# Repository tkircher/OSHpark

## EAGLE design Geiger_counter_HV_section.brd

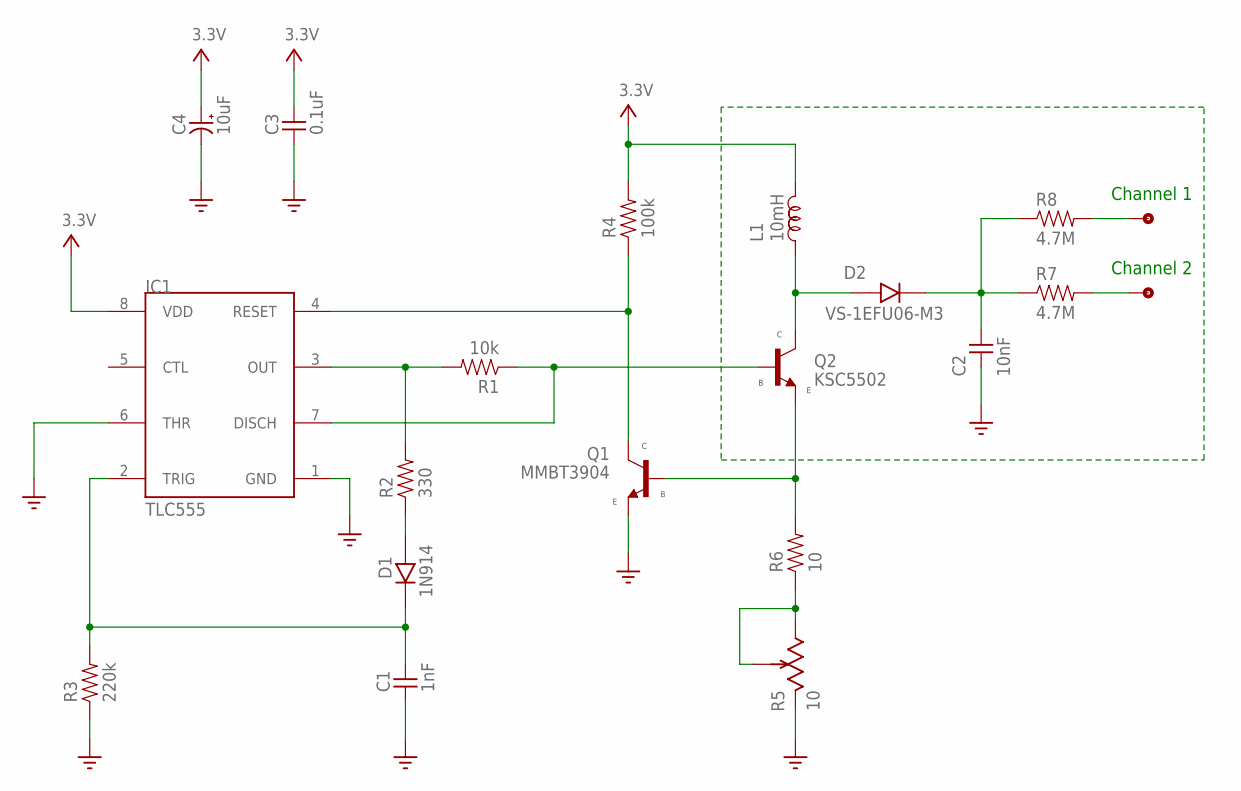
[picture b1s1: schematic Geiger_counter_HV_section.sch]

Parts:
C1: 1nF; 0805
C2: 10nF; 1206
C3: 0.1uF; 0805
C4: 10uF; 1206
D1: 1N914; 0805
D2: VS-1EFU06-M3; DO-219AB
IC1: TLC555; SOIC8
L1: 10mH; 1200LRS
Q1: MMBT3904; SOT-23A
Q2: KSC5502; TO-252
R1: 10k; 0805
R2: 330; 0805
R3: 220k; 0805
R4: 100k; 0805
R5: 10; 3362P
R6: 10; 1206
R7, R8: 4.7M; 1206
TP1, TP2: TP

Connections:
GND: C1.1, C2.1, C3.1, C4.2, IC1.1 (GND), IC1.6 (THR), Q1.3 (E), R3.1, R5.P$3 (P3)
unnamed: D1.1 (A), R2.1
unnamed: IC1.4 (RESET), Q1.1 (C), R4.1
unnamed: IC1.3 (OUT), R1.2, R2.2
unnamed: R5.P$1 (P1), R5.P$2 (WIPE), R6.1
unnamed: Q1.2 (B), Q2.P$2 (E), R6.2
unnamed: C1.2, D1.2 (K), IC1.2 (TRIG), R3.2
unnamed: IC1.7 (DISCH), Q2.P$1 (B), R1.1
unnamed: C2.2, D2.P$2 (K), R7.1, R8.1
unnamed: R7.2, TP1.P$1
unnamed: D2.P$1 (A), L1.P1 (1), Q2.P$3 (C)
unnamed: R8.2, TP2.P$1
VCC: C3.2, C4.1, IC1.8 (VDD), L1.P3 (2), R4.2

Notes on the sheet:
Channel 1
Channel 2

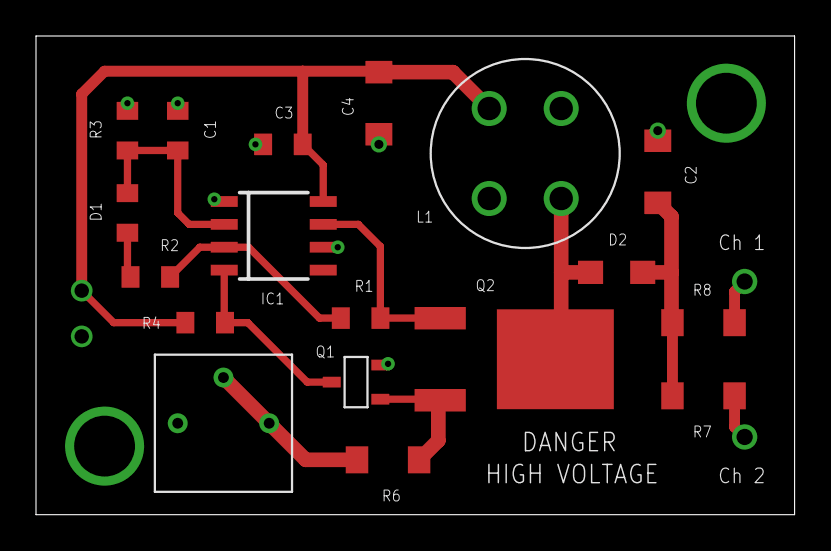
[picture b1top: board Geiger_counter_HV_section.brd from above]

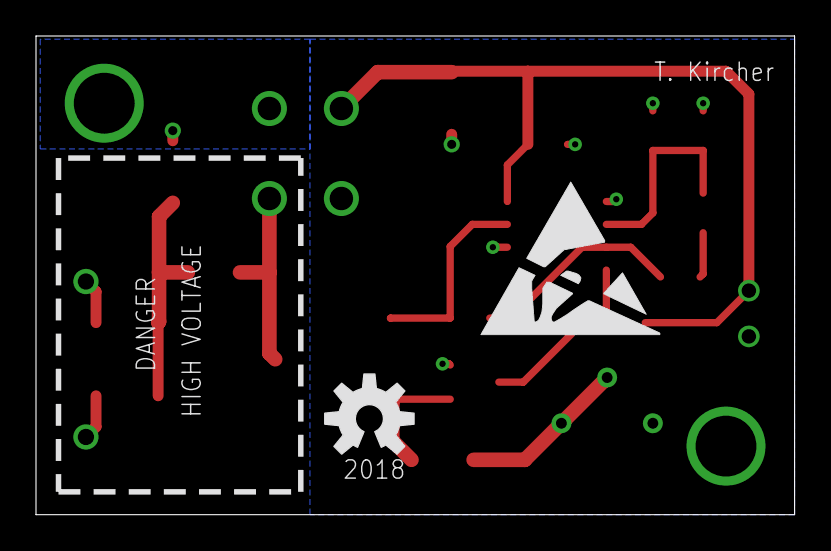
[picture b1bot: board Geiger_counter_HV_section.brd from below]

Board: 2 copper layers, 42.1 x 26.6 mm, 22 parts (2 on the bottom side), 13 nets.

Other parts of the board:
U$14: ESD_10.00
U$15: OSHW-LOGO-M

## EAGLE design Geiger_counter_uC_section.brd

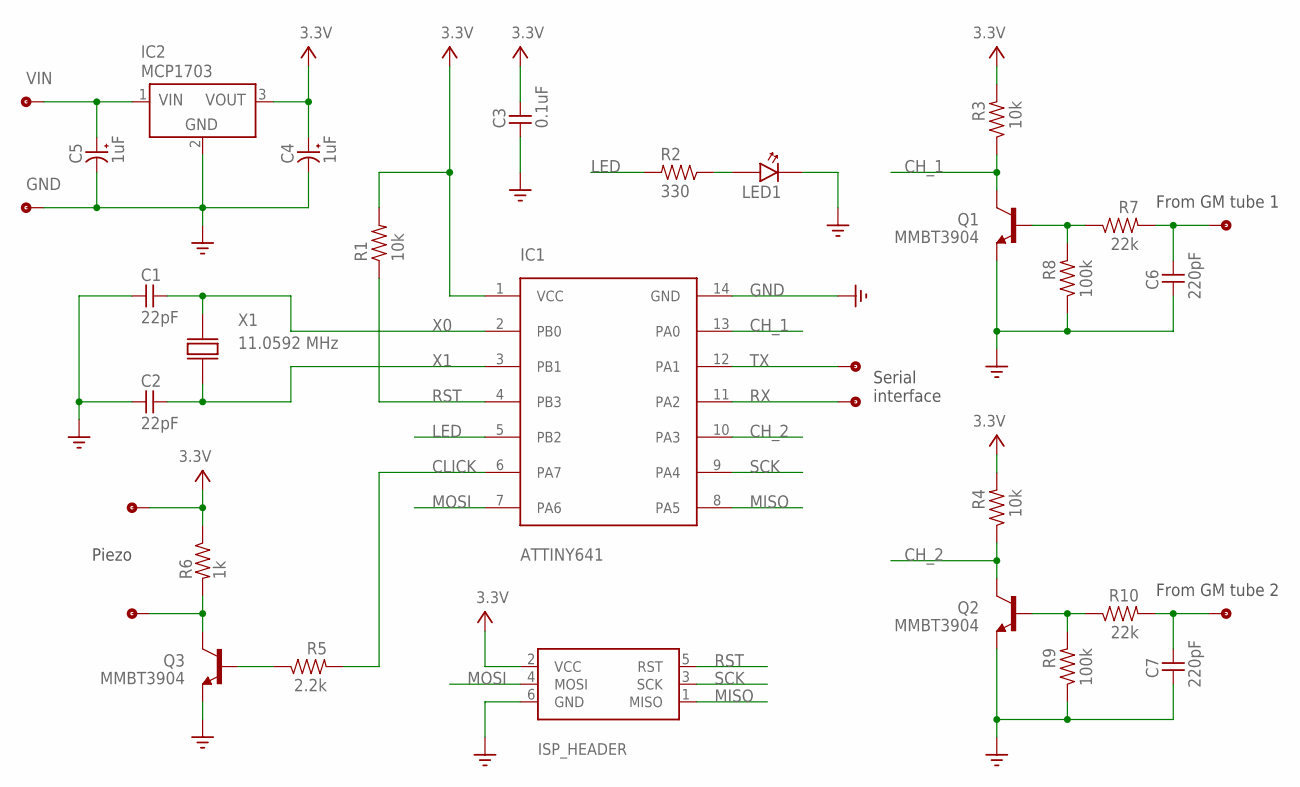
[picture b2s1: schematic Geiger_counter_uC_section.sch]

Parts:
C1, C2: 22pF; 0805
C3: 0.1uF; 0805
C4, C5: 1uF; 1206
C6, C7: 220pF; 0805
IC1: ATTINY641; SO14
IC2: MCP1703; SOT-23A
ISP_HEADER: ISP header; ISP_HEADER
LED1: LED0805; 0805
Q1, Q2, Q3: MMBT3904; SOT-23A
R1, R3, R4: 10k; 0805
R2: 330; 0805
R5: 2.2k; 0805
R6: 1k; 0805
R7, R10: 22k; 0805
R8, R9: 100k; 0805
TP1, TP2, TP3, TP4, TP7, TP8: TPSMALL; TP_SMALL
TP5, TP6: TP
X1: 11.0592 MHz; ABM3-2SMD

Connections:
3V3: C3.2, C4.1, IC1.1 (VCC), IC2.3 (VOUT), ISP_HEADER.2 (VCC), R1.2, R3.2, R4.2, R6.1, TP4.TP_SMALL
CH_1: IC1.13 (PA0), Q1.1 (C), R3.1
CH_2: IC1.10 (PA3), Q2.1 (C), R4.1
CLICK: IC1.6 (PA7), R5.2
GND: C1.1, C2.1, C3.1, C4.2, C5.2, C6.2, C7.2, IC1.14 (GND), IC2.2 (GND), ISP_HEADER.6 (GND), LED1.2 (K), Q1.3 (E), Q2.3 (E), Q3.3 (E), R8.1, R9.1, TP8.TP_SMALL
LED: IC1.5 (PB2), R2.2
MISO: IC1.8 (PA5), ISP_HEADER.1 (MISO)
MOSI: IC1.7 (PA6), ISP_HEADER.4 (MOSI)
unnamed: LED1.1 (A), R2.1
unnamed: Q3.2 (B), R5.1
unnamed: Q3.1 (C), R6.2, TP3.TP_SMALL
unnamed: Q1.2 (B), R7.1, R8.2
unnamed: C6.1, R7.2, TP5.P$1
unnamed: Q2.2 (B), R9.2, R10.1
unnamed: C7.1, R10.2, TP6.P$1
RST: IC1.4 (PB3), ISP_HEADER.5 (RST), R1.1
RX: IC1.11 (PA2), TP2.TP_SMALL
SCK: IC1.9 (PA4), ISP_HEADER.3 (SCK)
TX: IC1.12 (PA1), TP1.TP_SMALL
VIN: C5.1, IC2.1 (VIN), TP7.TP_SMALL
X0: C1.2, IC1.2 (PB0), X1.P$2 (2)
X1: C2.2, IC1.3 (PB1), X1.P$1 (1)

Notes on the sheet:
Serial interface
Piezo
From GM tube 1
From GM tube 2

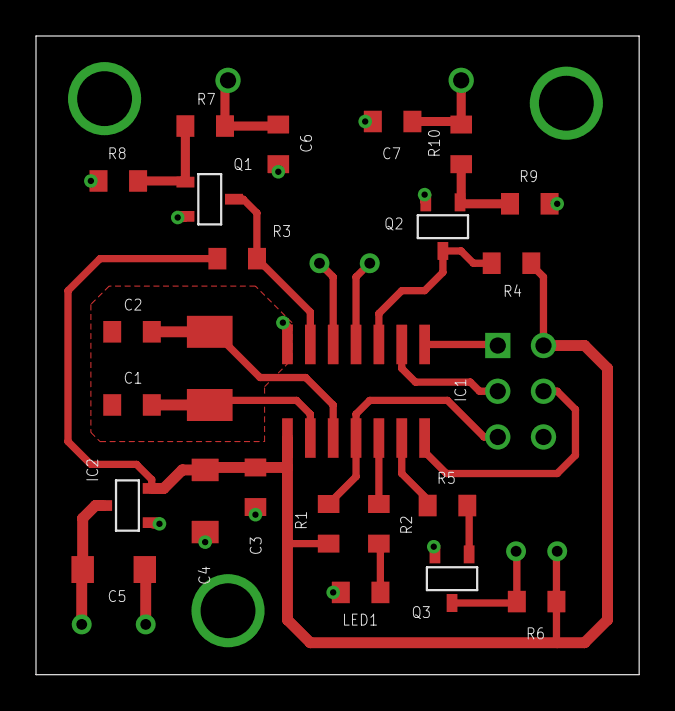
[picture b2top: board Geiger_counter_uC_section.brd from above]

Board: 2 copper layers, 33.5 x 35.5 mm, 34 parts (1 on the bottom side), 22 nets.

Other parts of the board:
U$17: OSHW-LOGO-M

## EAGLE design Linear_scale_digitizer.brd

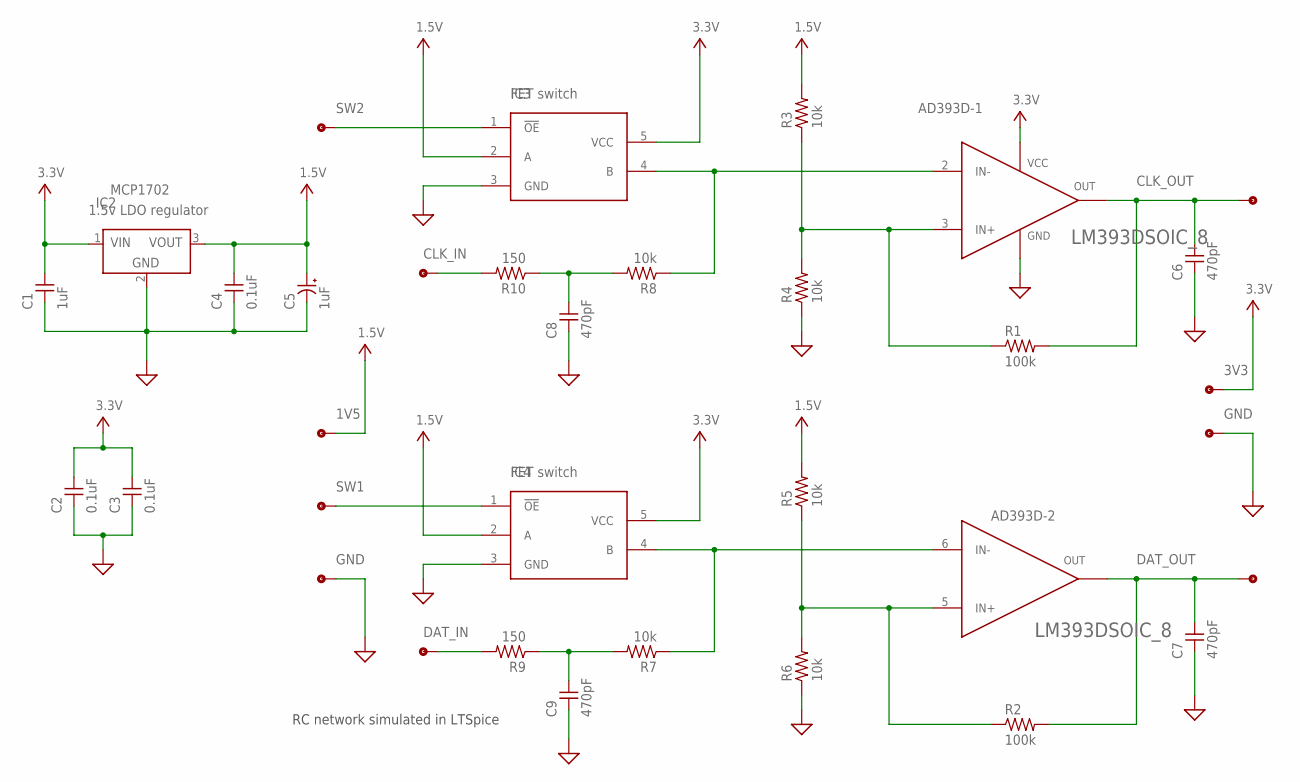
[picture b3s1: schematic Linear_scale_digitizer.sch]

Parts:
C1, C5: 1uF; 0805
C2, C3, C4: 0.1uF; 0805
C6, C7, C8, C9: 470pF; 0805
IC1: LM393DSOIC_8; SO_8
IC2: MCP1702; SOT-23A
IC3, IC4: SN74CB3T1G125; SOT_23-5
R1, R2: 100k; 0805
R3, R4, R5, R6, R7, R8: 10k; 0805
R9, R10: 150; 0805
TP1, TP2, TP3, TP4, TP5, TP6, TP7, TP8, TP9, TP10: TP

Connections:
1V5: C4.2, C5.1, IC2.3 (VOUT), IC3.2 (A), IC4.2 (A), R3.2, R5.2, TP7.P$1
3V3: C1.2, C2.2, C3.2, IC1.8 (VCC), IC2.1 (VIN), IC3.5 (VCC), IC4.5 (VCC), TP10.P$1
CLK_IN: R10.2, TP5.P$1
CLK_OUT: C6.2, IC1.1 (OUT), R1.2, TP1.P$1
DAT_IN: R9.2, TP6.P$1
DAT_OUT: C7.2, IC1.7 (OUT), R2.2, TP2.P$1
GND: C1.1, C2.1, C3.1, C4.1, C5.2, C6.1, C7.1, C8.1, C9.1, IC1.4 (GND), IC2.2 (GND), IC3.3 (GND), IC4.3 (GND), R4.1, R6.1, TP8.P$1, TP9.P$1
unnamed: IC1.5 (IN+), R2.1, R5.1, R6.2
unnamed: IC1.3 (IN+), R1.1, R3.1, R4.2
unnamed: C8.2, R8.2, R10.1
unnamed: IC1.6 (IN-), IC4.4 (B), R7.1
unnamed: IC1.2 (IN-), IC3.4 (B), R8.1
unnamed: C9.2, R7.2, R9.1
SW1: IC4.1 (!OE), TP4.P$1
SW2: IC3.1 (!OE), TP3.P$1

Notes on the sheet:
1.5v LDO regulator
FET switch
AD393D-2
AD393D-1
RC network simulated in LTSpice

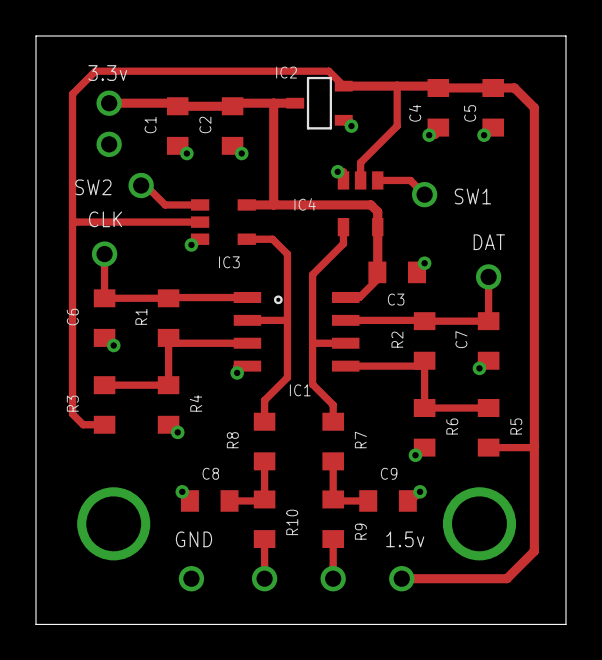
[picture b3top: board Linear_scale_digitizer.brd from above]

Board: 2 copper layers, 29.4 x 32.7 mm, 34 parts (1 on the bottom side), 15 nets.

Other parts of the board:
U$7: ESD_10.00

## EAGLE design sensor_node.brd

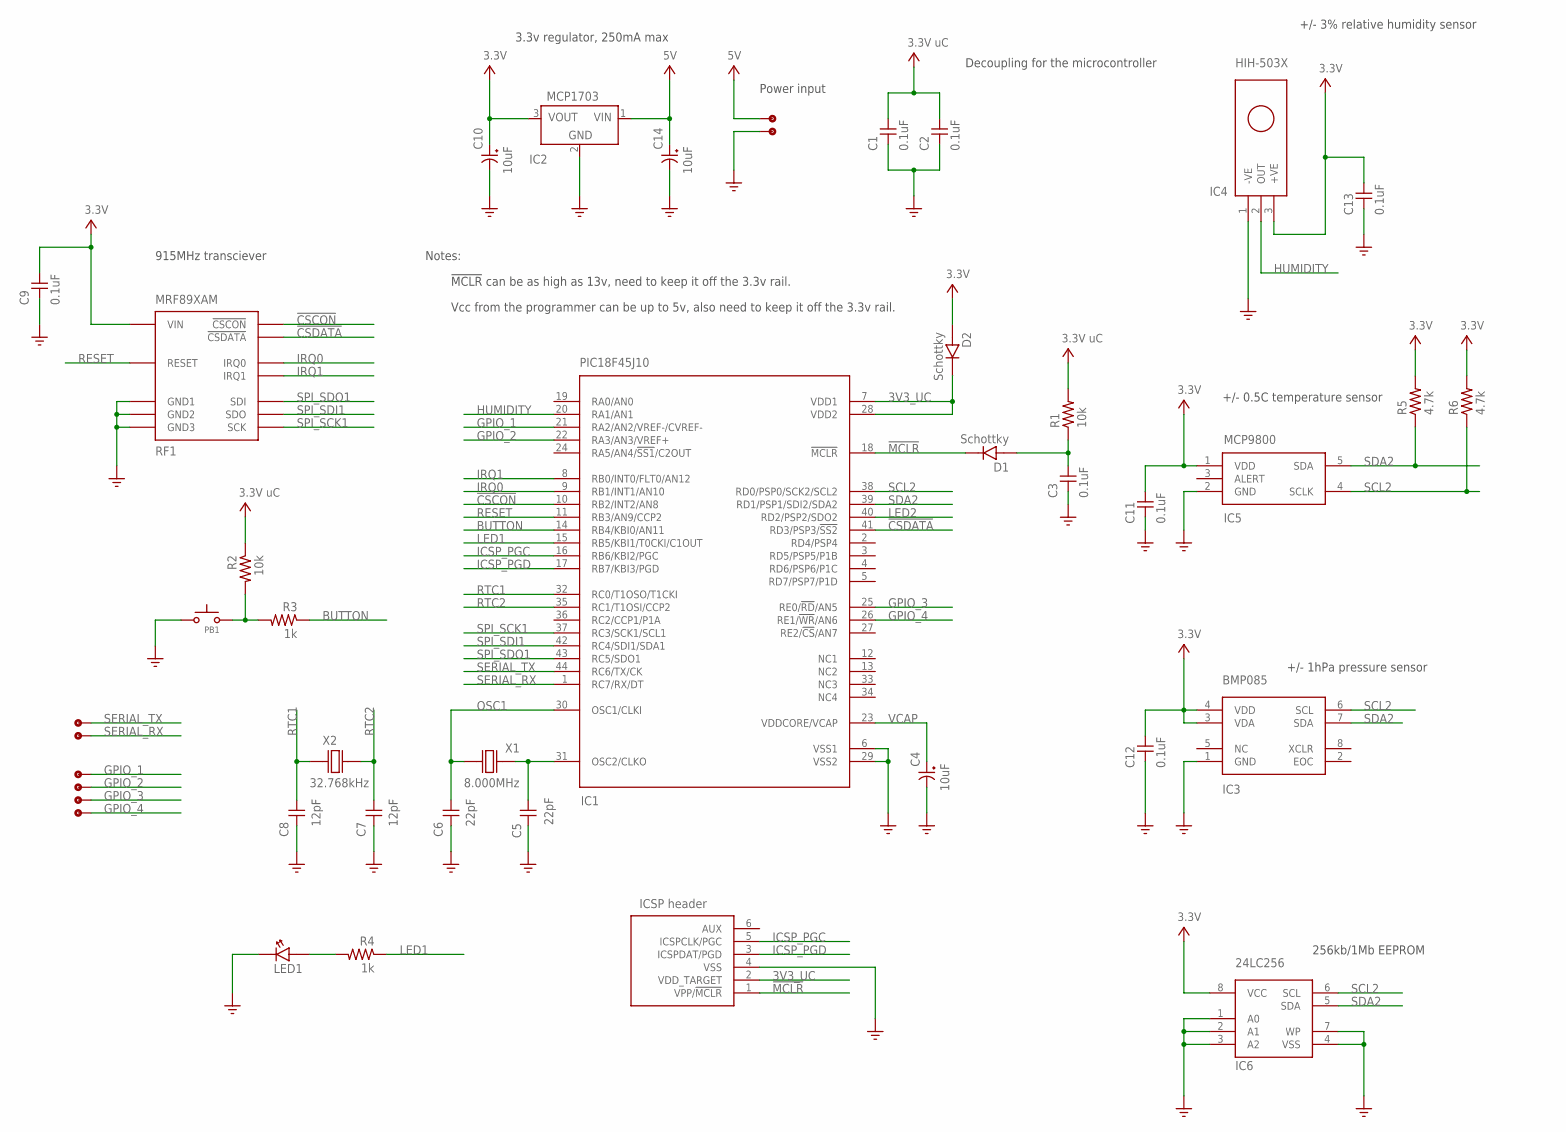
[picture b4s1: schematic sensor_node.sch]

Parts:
C1, C2, C3, C9, C11, C12, C13: 0.1uF; 0805
C4, C10, C14: 10uF; 1206
C5, C6: 22pF; 0805
C7, C8: 12pF; 0805
CONN1: ICSP header; ISP_HEADER
D1, D2: Schottky; 0805
IC1: PIC18F45J10; TQFP_44
IC2: MCP1703; SOT-23A
IC3: BMP085; LCC8
IC4: HIH-503X; HIH_503X
IC5: MCP9800; SOT_23-5
IC6: 24LC256; SO_8
LED1: LED0805; 0805
PB1: BUTTON_2PADS; BUTTON_4SMD
R1, R2: 10k; 0805
R3, R4: 1k; 0805
R5, R6: 4.7k; 0805
RF1: MRF89XAM
TP1, TP2, TP3, TP4, TP5, TP6, TP7, TP8: TP
X1: 8.000MHz; NX5032
X2: 32.768kHz; CM200C

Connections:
3V3: C9.2, C10.1, C11.2, C12.2, C13.2, D2.1 (A), IC2.3 (VOUT), IC3.3 (VDA), IC3.4 (VDD), IC4.3 (+VE), IC5.1 (VDD), IC6.8 (VCC), R5.2, R6.2, RF1.VIN
3V3_UC: C1.2, C2.2, CONN1.2 (VDD_TARGET), D2.2 (K), IC1.7 (VDD1), IC1.28 (VDD2), R1.2, R2.1
5V: C14.1, IC2.1 (VIN), TP3.P$1
!CSCON!: IC1.10 (RB2/INT2/AN8), RF1.!CSCON
!CSDATA!: IC1.41 (RD3/PSP3/!SS2!), RF1.!CSDATA
!MCLR!: CONN1.1 (VPP/!MCLR!), D1.2 (K), IC1.18 (!MCLR!)
BUTTON: IC1.14 (RB4/KBI0/AN11), R3.1
GND: C1.1, C2.1, C3.1, C4.2, C5.2, C6.2, C7.2, C8.2, C9.1, C10.2, C11.1, C12.1, C13.1, C14.2, CONN1.4 (VSS), IC1.6 (VSS1), IC1.29 (VSS2), IC2.2 (GND), IC3.1 (GND), IC4.1 (-VE), IC5.2 (GND), IC6.1 (A0), IC6.2 (A1), IC6.3 (A2), IC6.4 (VSS), IC6.7 (WP), LED1.2 (K), PB1.3, RF1.GND1, RF1.GND2, RF1.GND3, TP4.P$1
GPIO_1: IC1.21 (RA2/AN2/VREF-/CVREF-), TP6.P$1
GPIO_2: IC1.22 (RA3/AN3/VREF+), TP5.P$1
GPIO_3: IC1.25 (RE0/!RD!/AN5), TP7.P$1
GPIO_4: IC1.26 (RE1/!WR!/AN6), TP8.P$1
HUMIDITY: IC1.20 (RA1/AN1), IC4.2 (OUT)
ICSP_PGC: CONN1.5 (ICSPCLK/PGC), IC1.16 (RB6/KBI2/PGC)
ICSP_PGD: CONN1.3 (ICSPDAT/PGD), IC1.17 (RB7/KBI3/PGD)
IRQ0: IC1.9 (RB1/INT1/AN10), RF1.IRQ0
IRQ1: IC1.8 (RB0/INT0/FLT0/AN12), RF1.IRQ1
LED1: IC1.15 (RB5/KBI1/T0CKI/C1OUT), R4.1
LED2: IC1.40 (RD2/PSP2/SDO2)
unnamed: LED1.1 (A), R4.2
unnamed: C3.2, D1.1 (A), R1.1
unnamed: PB1.1, R2.2, R3.2
OSC1: C6.1, IC1.30 (OSC1/CLKI), X1.P$1 (1)
OSC2: C5.1, IC1.31 (OSC2/CLKO), X1.P$2 (2)
RESET: IC1.11 (RB3/AN9/CCP2), RF1.RESET
RTC1: C8.1, IC1.32 (RC0/T1OSO/T1CKI), X2.OSC2 (2)
RTC2: C7.1, IC1.35 (RC1/T1OSI/CCP2), X2.OSC1 (1)
SCL2: IC1.38 (RD0/PSP0/SCK2/SCL2), IC3.6 (SCL), IC5.4 (SCLK), IC6.6 (SCL), R6.1
SDA2: IC1.39 (RD1/PSP1/SDI2/SDA2), IC3.7 (SDA), IC5.5 (SDA), IC6.5 (SDA), R5.1
SERIAL_RX: IC1.1 (RC7/RX/DT), TP2.P$1
SERIAL_TX: IC1.44 (RC6/TX/CK), TP1.P$1
SPI_SCK1: IC1.37 (RC3/SCK1/SCL1), RF1.SCK
SPI_SDI1: IC1.42 (RC4/SDI1/SDA1), RF1.SDO
SPI_SDO1: IC1.43 (RC5/SDO1), RF1.SDI
VCAP: C4.1, IC1.23 (VDDCORE/VCAP)

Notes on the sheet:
915MHz transciever
+/- 0.5C temperature sensor
+/- 1hPa pressure sensor
+/- 3% relative humidity sensor
3.3v regulator, 250mA max
Power input
256kb/1Mb EEPROM
!MCLR! can be as high as 13v, need to keep it off the 3.3v rail.
Vcc from the programmer can be up to 5v, also need to keep it off the 3.3v rail.
Notes:
Decoupling for the microcontroller

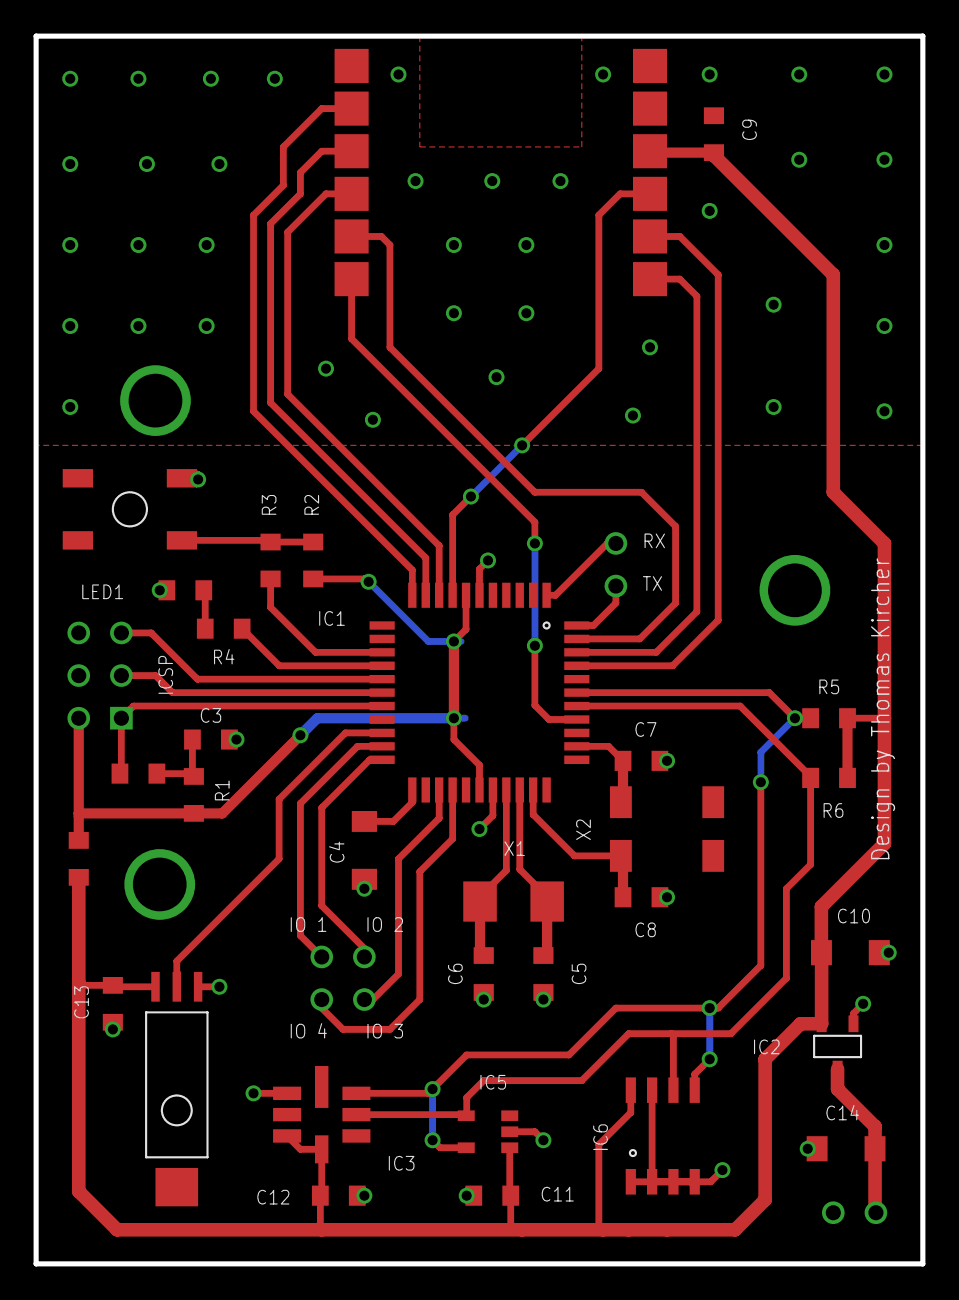
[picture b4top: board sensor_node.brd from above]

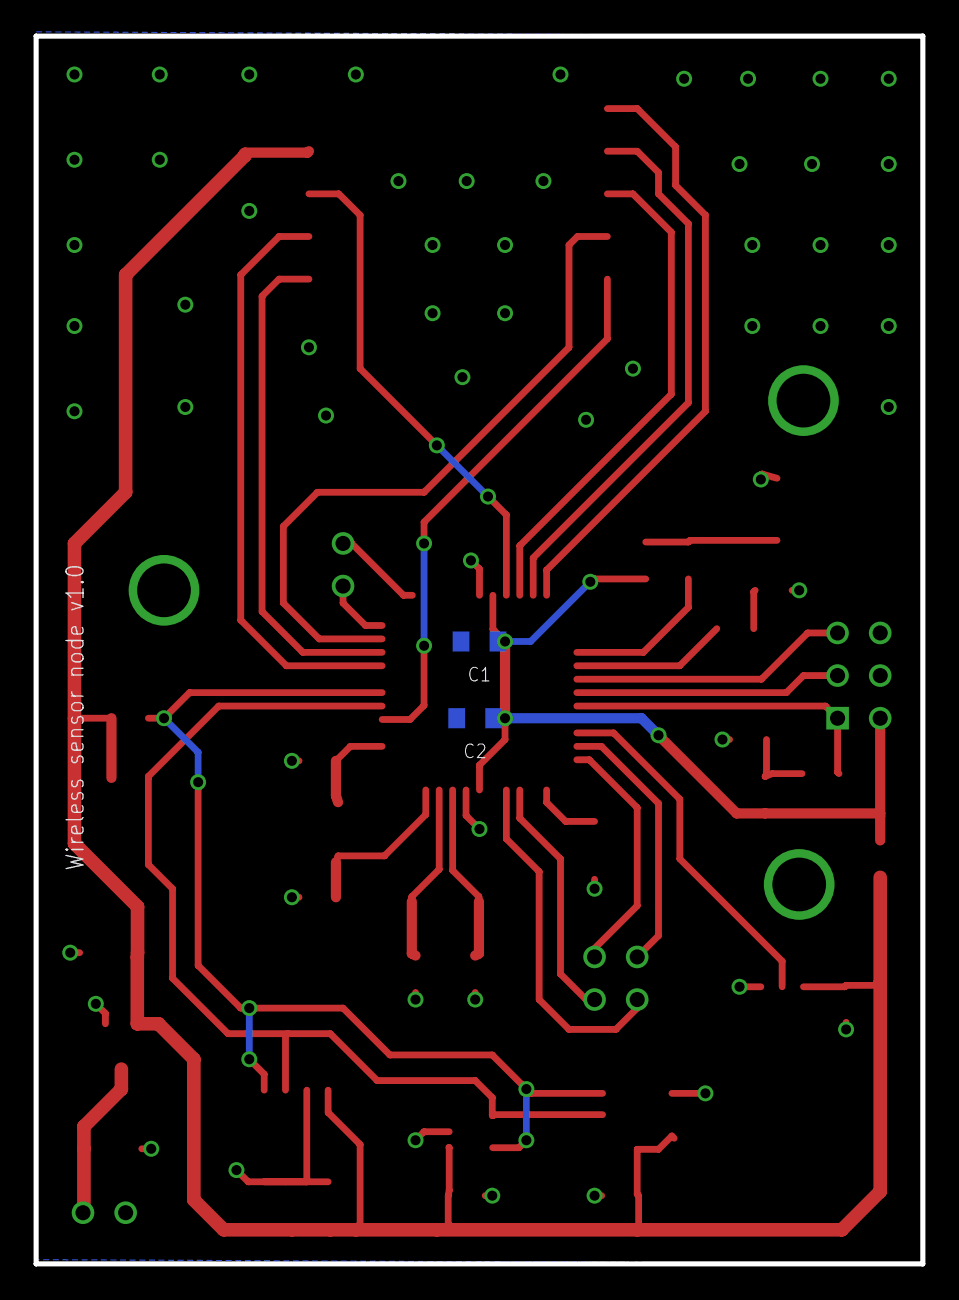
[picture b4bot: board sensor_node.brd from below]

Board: 2 copper layers, 52.8 x 73.2 mm, 43 parts (3 on the bottom side), 34 nets.

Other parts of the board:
OSHLOGO: OSHLOGO

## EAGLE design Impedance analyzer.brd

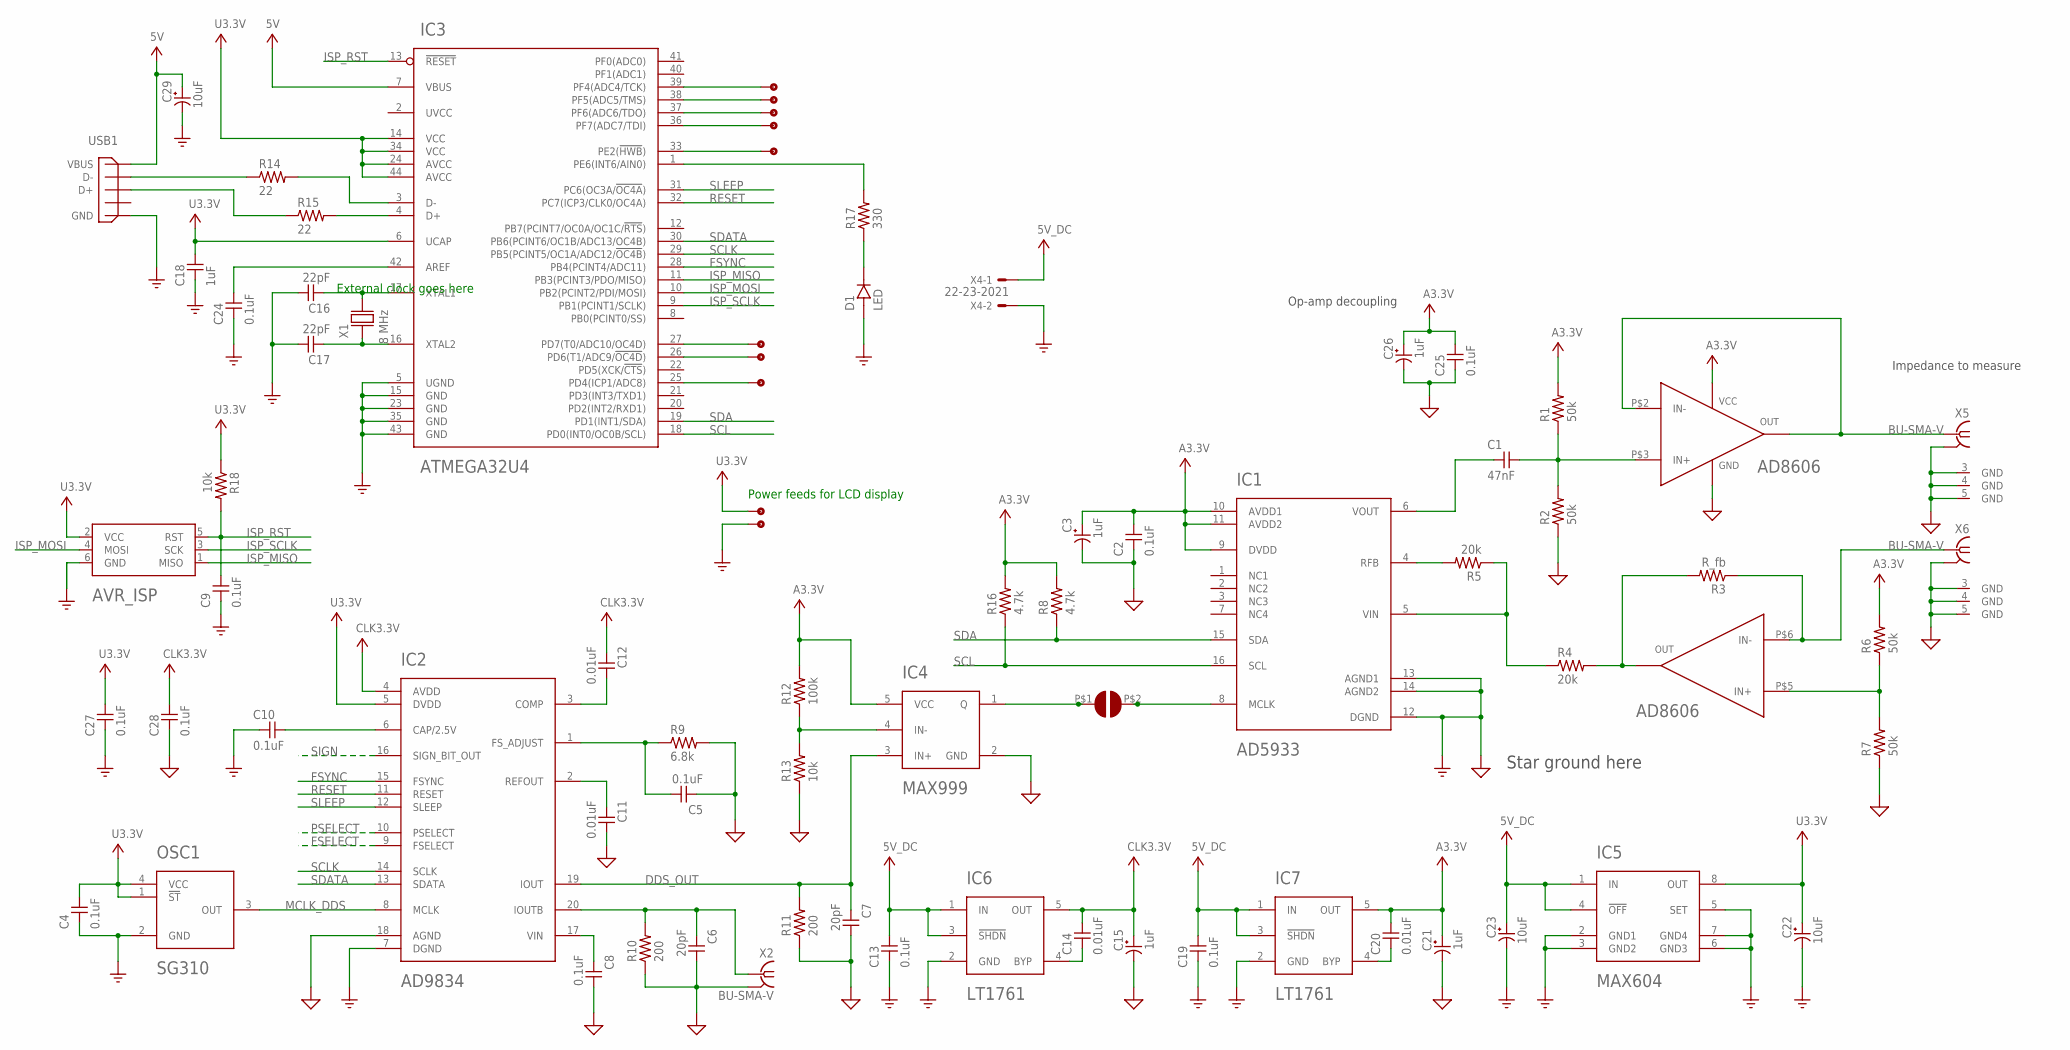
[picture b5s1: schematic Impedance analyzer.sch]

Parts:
C1: 47nF; 0805
C2, C4, C5, C8, C9, C10, C13, C19, C24, C25, C27, C28: 0.1uF; 0805
C3, C15, C21, C26: 1uF; 1206
C6, C7: 20pF; 0805
C11, C12, C14, C20: 0.01uF; 0805
C16, C17: 22pF; 0805
C18: 1uF; 0805
C22, C23, C29: 10uF; 1206
D1: LED; 0805
IC1: AD5933; SSOP_16
IC2: AD9834; TSSOP_20
IC3: ATMEGA32U4; TQFP_44
IC4: MAX999; SOT_23-5
IC5: MAX604; SO_8
IC6, IC7: LT1761; TSOT-23
IC8: AD8606; MSOP_8
OSC1: SG310
R1, R2, R6, R7: 50k; 0805
R3: R_fb; 0805
R4, R5: 20k; 0805
R8, R16: 4.7k; 0805
R9: 6.8k; 0805
R10, R11: 200; 0805
R12: 100k; 0805
R13, R18: 10k; 0805
R14, R15: 22; 0805
R17: 330; 0805
TP1, TP2, TP3, TP4, TP5, TP6, TP7, TP10, TP11, TP12: TPSMALL; TP_SMALL
U$41: ISP_HEADER
U$57: JUMPER
USB1: USB_MINIUX60-MB-5ST; USB_MINI
X1: 8 MHz; NX5032
X2, X5, X6: BU-SMA-V
X4: 22-23-2021

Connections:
5V_DC: C13.2, C19.2, C23.1, IC5.1 (IN), IC5.4 (!OFF), IC6.1 (IN), IC6.3 (!SHDN), IC7.1 (IN), IC7.3 (!SHDN), X4.1
5V_USB: C29.1, IC3.7 (VBUS), USB1.1 (VBUS)
A3V3: C2.2, C3.1, C20.2, C21.1, C25.2, C26.1, IC1.9 (DVDD), IC1.10 (AVDD1), IC1.11 (AVDD2), IC4.5 (VCC), IC7.5 (OUT), IC8.P$8 (VCC), R1.2, R6.2, R8.2, R12.2, R16.2
CLK3V3: C12.1, C14.2, C15.1, C28.2, IC2.4 (AVDD), IC6.5 (OUT)
DDS_OUT: C7.1, IC2.19 (IOUT), IC4.3 (IN+), R11.2
FSELECT: IC2.9 (FSELECT)
FSYNC: IC2.15 (FSYNC), IC3.28 (PB4(PCINT4/ADC11))
GND: C2.1, C3.2, C4.1, C5.1, C6.2, C7.2, C8.2, C9.1, C10.1, C11.2, C13.1, C15.2, C16.2, C17.2, C18.1, C19.1, C21.2, C22.2, C23.2, C24.1, C25.1, C26.2, C27.1, C28.1, C29.2, D1.1 (A), IC1.12 (DGND), IC1.13 (AGND1), IC1.14 (AGND2), IC2.7 (DGND), IC2.18 (AGND), IC3.5 (UGND), IC3.15 (GND), IC3.23 (GND), IC3.35 (GND), IC3.43 (GND), IC4.2 (GND), IC5.2 (GND1), IC5.3 (GND2), IC5.5 (SET), IC5.6 (GND3), IC5.7 (GND4), IC6.2 (GND), IC7.2 (GND), IC8.P$4 (GND), OSC1.2 (GND), R2.1, R7.1, R9.2, R10.1, R11.1, R13.1, TP11.TP_SMALL, U$41.6 (GND), USB1.5 (GND), X2.2 (GND), X2.3 (GND), X2.4 (GND), X2.5 (GND), X4.2, X5.2 (GND), X5.3 (GND), X5.4 (GND), X5.5 (GND), X6.2 (GND), X6.3 (GND), X6.4 (GND), X6.5 (GND)
ISP_MISO: IC3.11 (PB3(PCINT3/PDO/MISO)), U$41.1 (MISO)
ISP_MOSI: IC3.10 (PB2(PCINT2/PDI/MOSI)), U$41.4 (MOSI)
ISP_RST: C9.2, IC3.13 (!RESET!), R18.2, U$41.5 (RST)
ISP_SCLK: IC3.9 (PB1(PCINT1/SCLK)), U$41.3 (SCK)
MCLK_DDS: IC2.8 (MCLK), OSC1.3 (OUT)
unnamed: C1.2, IC8.P$3 (IN+), R1.1, R2.2
unnamed: IC8.P$1 (OUT), IC8.P$2 (IN-), X5.1
unnamed: IC8.P$6 (IN-), R3.1, X6.1
unnamed: IC8.P$7 (OUT), R3.2, R4.2
unnamed: IC8.P$5 (IN+), R6.1, R7.2
unnamed: IC1.4 (RFB), R5.2
unnamed: IC1.5 (VIN), R4.1, R5.1
unnamed: C1.1, IC1.6 (VOUT)
unnamed: IC3.1 (PE6(INT6/AIN0)), R17.2
unnamed: C24.2, IC3.42 (AREF)
unnamed: C5.2, IC2.1 (FS_ADJUST), R9.1
unnamed: C6.1, IC2.20 (IOUTB), R10.2, X2.1
unnamed: C10.2, IC2.6 (CAP/2.5V)
unnamed: C11.1, IC2.2 (REFOUT)
unnamed: D1.2 (K), R17.1
unnamed: C8.1, IC2.17 (VIN)
unnamed: C12.2, IC2.3 (COMP)
unnamed: IC3.27 (PD7(T0/ADC10/OC4D)), TP1.TP_SMALL
unnamed: C14.1, IC6.4 (BYP)
unnamed: IC3.26 (PD6(T1/ADC9/!OC4D!)), TP2.TP_SMALL
unnamed: IC3.39 (PF4(ADC4/TCK)), TP3.TP_SMALL
unnamed: IC4.4 (IN-), R12.1, R13.2
unnamed: IC3.4 (D+), R15.2
unnamed: R15.1, USB1.3 (D+)
unnamed: R14.1, USB1.2 (D-)
unnamed: IC3.3 (D-), R14.2
unnamed: C16.1, IC3.17 (XTAL1), X1.P$2 (2)
unnamed: C17.1, IC3.16 (XTAL2), X1.P$1 (1)
unnamed: IC3.38 (PF5(ADC5/TMS)), TP4.TP_SMALL
unnamed: C20.1, IC7.4 (BYP)
unnamed: IC3.37 (PF6(ADC6/TDO)), TP5.TP_SMALL
unnamed: IC3.36 (PF7(ADC7/TDI)), TP6.TP_SMALL
unnamed: IC3.25 (PD4(ICP1/ADC8)), TP7.TP_SMALL
unnamed: IC4.1 (Q), U$57.P$1
unnamed: IC1.8 (MCLK), U$57.P$2
unnamed: IC3.33 (PE2(!HWB!)), TP12.TP_SMALL
PSELECT: IC2.10 (PSELECT)
RESET: IC2.11 (RESET), IC3.32 (PC7(ICP3/CLK0/OC4A))
SCL: IC1.16 (SCL), IC3.18 (PD0(INT0/OC0B/SCL)), R16.1
SCLK: IC2.14 (SCLK), IC3.29 (PB5(PCINT5/OC1A/ADC12/!OC4B!))
SDA: IC1.15 (SDA), IC3.19 (PD1(INT1/SDA)), R8.1
SDATA: IC2.13 (SDATA), IC3.30 (PB6(PCINT6/OC1B/ADC13/OC4B))
SIGN: IC2.16 (SIGN_BIT_OUT)
SLEEP: IC2.12 (SLEEP), IC3.31 (PC6(OC3A/!OC4A!))
U3V3: C4.2, C18.2, C22.1, C27.2, IC2.5 (DVDD), IC3.6 (UCAP), IC3.14 (VCC), IC3.24 (AVCC), IC3.34 (VCC), IC3.44 (AVCC), IC5.8 (OUT), OSC1.1 (!ST), OSC1.4 (VCC), R18.1, TP10.TP_SMALL, U$41.2 (VCC)

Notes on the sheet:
Impedance to measure
Op-amp decoupling
Star ground here
External clock goes here
Power feeds for LCD display

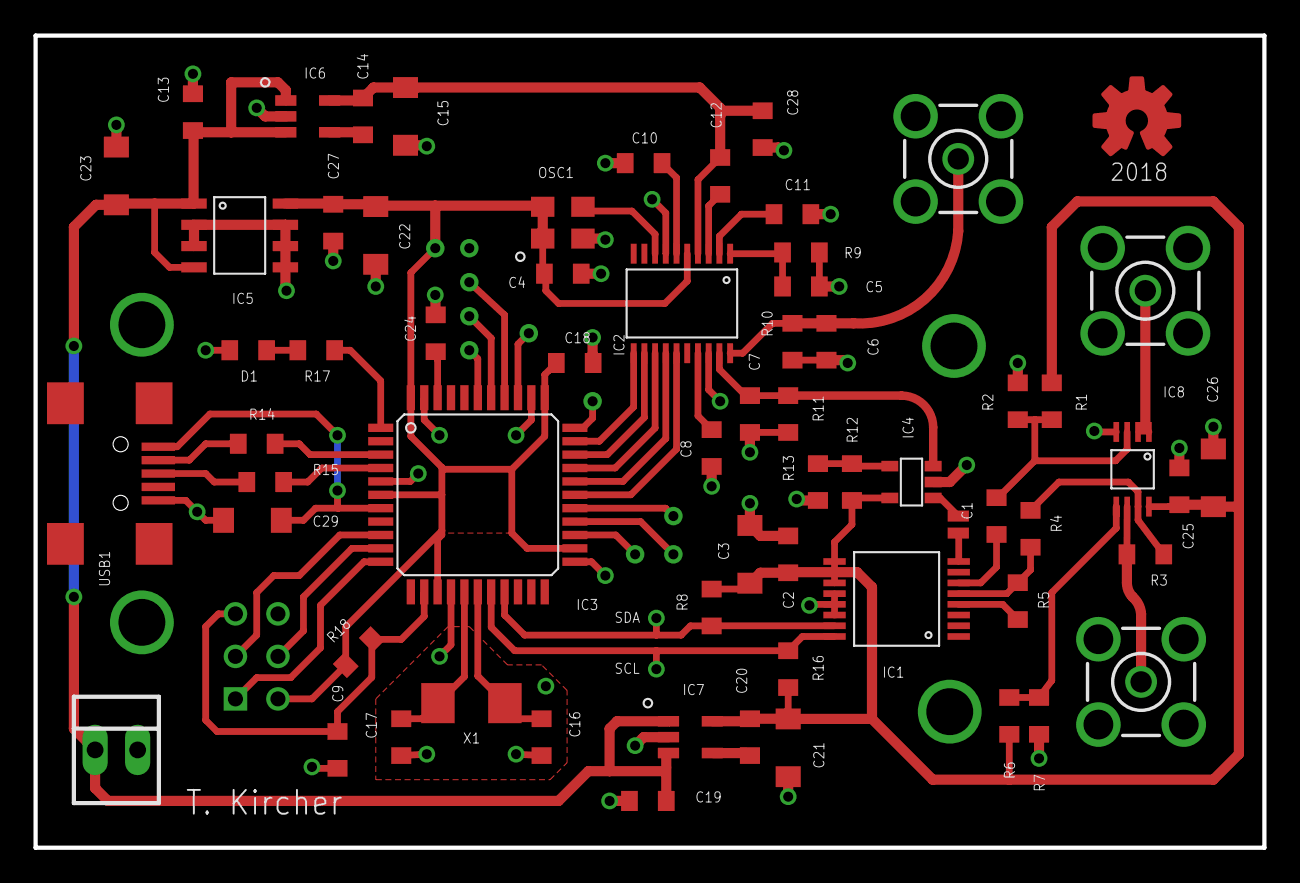
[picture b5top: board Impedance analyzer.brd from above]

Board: 2 copper layers, 73.4 x 48.5 mm, 76 parts (1 on the bottom side), 55 nets.

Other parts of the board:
U$1: OSHWLOGO_TOP_0.2

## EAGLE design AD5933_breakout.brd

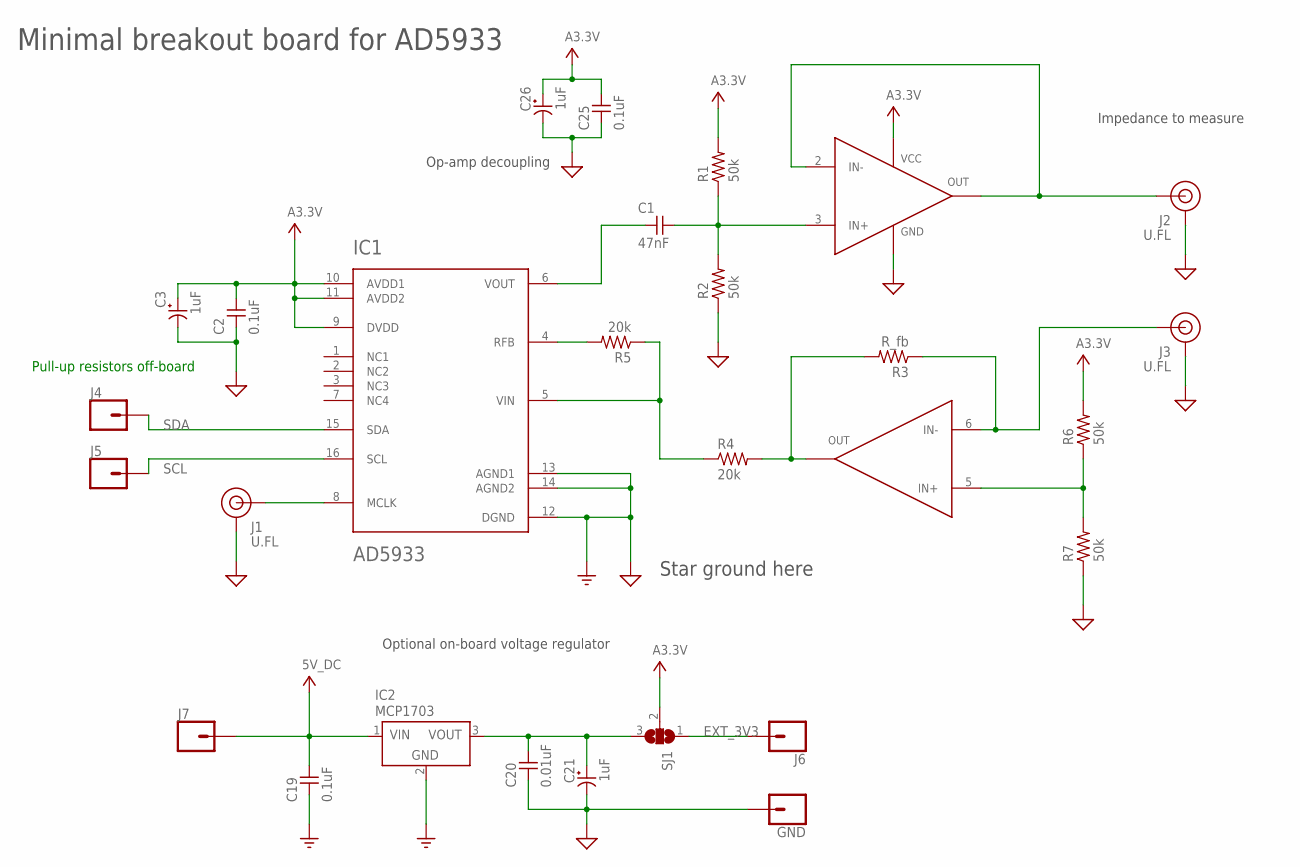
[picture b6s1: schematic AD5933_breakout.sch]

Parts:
C1: 47nF; 0805
C2, C19, C25: 0.1uF; 0805
C3, C21, C26: 1uF; 1206
C20: 0.01uF; 0805
GND: CONN_01PTH_NO_SILK_YES_STOP; 1X01_NO_SILK
IC1: AD5933; SSOP_16
IC2: MCP1703; SOT-23A
IC8: AD8606SOIC_8; SO_8
J1, J2, J3: U.FL
J4, J5, J6, J7: CONN_01PTH_NO_SILK_YES_STOP; 1X01_NO_SILK
R1, R2, R6, R7: 50k; 0805
R3: R_fb; 0805
R4, R5: 20k; 0805
SJ1: SJ2W; SJ_2

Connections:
3V3: C2.2, C3.1, C25.2, C26.1, IC1.9 (DVDD), IC1.10 (AVDD1), IC1.11 (AVDD2), IC8.8 (VCC), R1.2, R6.2, SJ1.2
5V_DC: C19.2, IC2.1 (VIN), J7.1
EXT_3V3: J6.1, SJ1.1
GND: C2.1, C3.2, C19.1, C20.1, C21.2, C25.1, C26.2, GND.1, IC1.12 (DGND), IC1.13 (AGND1), IC1.14 (AGND2), IC2.2 (GND), IC8.4 (GND), J1.1 (GND), J1.2 (GND), J2.1 (GND), J2.2 (GND), J3.1 (GND), J3.2 (GND), R2.1, R7.1
INT_3V3: C20.2, C21.1, IC2.3 (VOUT), SJ1.3
unnamed: C1.2, IC8.3 (IN+), R1.1, R2.2
unnamed: IC8.1 (OUT), IC8.2 (IN-), J2.FEED (SIGNAL)
unnamed: IC8.6 (IN-), J3.FEED (SIGNAL), R3.1
unnamed: IC8.7 (OUT), R3.2, R4.2
unnamed: IC8.5 (IN+), R6.1, R7.2
unnamed: IC1.4 (RFB), R5.2
unnamed: IC1.5 (VIN), R4.1, R5.1
unnamed: C1.1, IC1.6 (VOUT)
unnamed: IC1.8 (MCLK), J1.FEED (SIGNAL)
SCL: IC1.16 (SCL), J5.1
SDA: IC1.15 (SDA), J4.1

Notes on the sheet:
Impedance to measure
Op-amp decoupling
Star ground here
Optional on-board voltage regulator
Pull-up resistors off-board
Minimal breakout board for AD5933

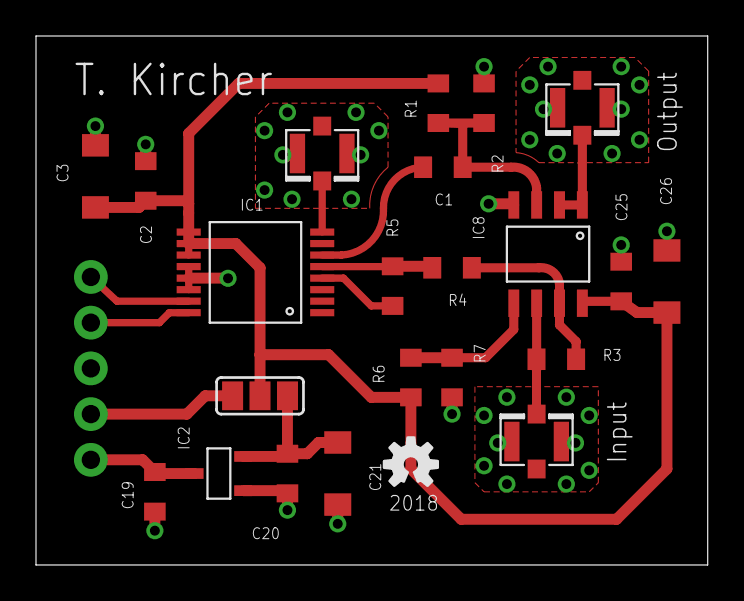
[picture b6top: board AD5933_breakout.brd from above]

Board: 2 copper layers, 37.3 x 29.4 mm, 29 parts (1 on the bottom side), 16 nets.

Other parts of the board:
U$13: OSHW-LOGO-S
U$14: ESD_10.00

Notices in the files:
parts and their libraries:
SparkFun-Connectors: Licensing: Creative Commons ShareAlike 4.0 International - https://creativecommons.org/licenses/by-sa/4.0
